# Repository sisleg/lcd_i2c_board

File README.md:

A small interface bord used to connect a LCD character or a OLed character
display that uses the classic HD44780 protocol. Via a I2C buss to any microcontroller.

A MCP23017 from Microchip is used. That ccontroller has two 8 bit ports. One is 
used as the databus to the Display. The other port is used for controll lines (3 bits), contoling a backlight or a external led (1 bit). The last four bits is
used for a simple keybord interface.

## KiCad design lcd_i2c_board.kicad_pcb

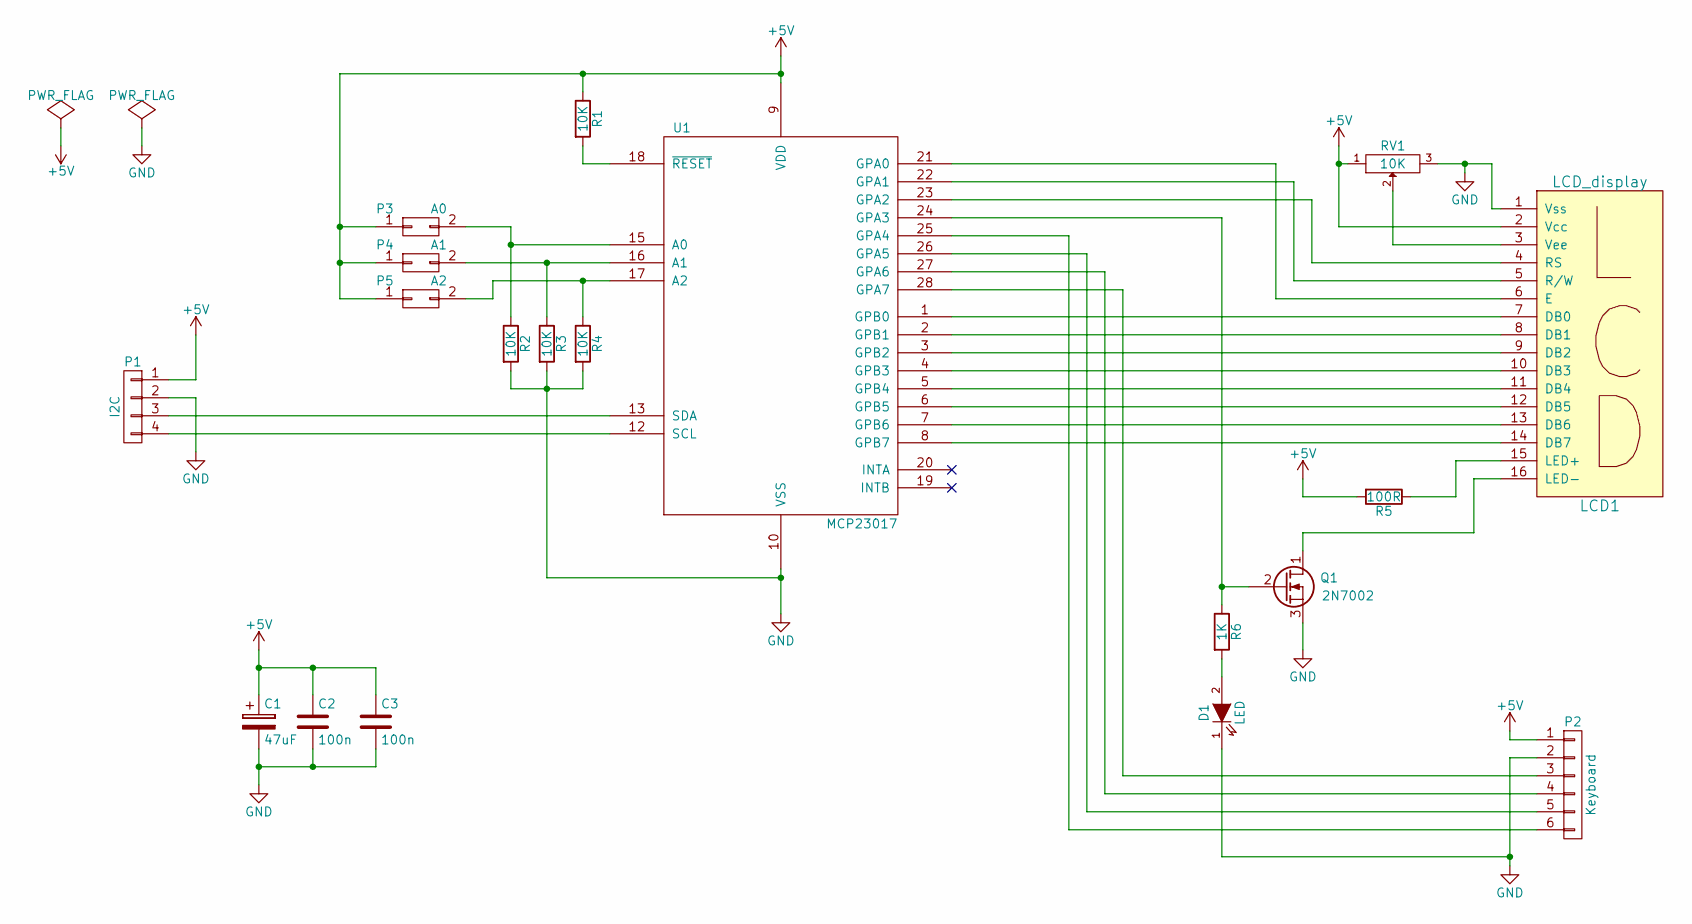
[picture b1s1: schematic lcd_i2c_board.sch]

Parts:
C1: 47uF; c_elec_6.3x7.7
C2, C3: 100n; C_1206_HandSoldering
D1: LED; MOLEX-22-05-3021
LCD1: LCD_display; Pin_Header_Straight_1x16
P1: I2C; MOLEX-22-05-3041
P2: Keyboard; MOLEX-22-05-3061
P3: A0; R_0805_HandSoldering
P4: A1; R_0805_HandSoldering
P5: A2; R_0805_HandSoldering
Q1: 2N7002; SOT-23_Handsoldering
R1, R2, R3, R4: 10K; R_0805_HandSoldering
R5: 100R; R_0805_HandSoldering
R6: 1K; R_0805_HandSoldering
RV1: 10K; Potentiometer_Trimmer-Suntan-TSR-3386P
U1: MCP23017; SOIC-28W_7.5x17.9mm_Pitch1.27mm

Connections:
+5V: C1.1, C2.1, C3.1, LCD1.2 (Vcc), P1.1, P2.1, P3.1, P4.1, P5.1, R1.1, R5.2, RV1.1, U1.9 (VDD)
GND: C1.2, C2.2, C3.2, D1.1 (K), LCD1.1 (Vss), P1.2, P2.2, Q1.3 (S), R2.2, R3.2, R4.2, RV1.3, U1.10 (VSS)
unnamed: D1.2 (A), R6.2
unnamed: LCD1.3 (Vee), RV1.2
unnamed: LCD1.4 (RS), U1.23 (GPA2)
unnamed: LCD1.5 (R/W), U1.22 (GPA1)
unnamed: LCD1.6 (E), U1.21 (GPA0)
unnamed: LCD1.7 (DB0), U1.1 (GPB0)
unnamed: LCD1.8 (DB1), U1.2 (GPB1)
unnamed: LCD1.9 (DB2), U1.3 (GPB2)
unnamed: LCD1.10 (DB3), U1.4 (GPB3)
unnamed: LCD1.11 (DB4), U1.5 (GPB4)
unnamed: LCD1.12 (DB5), U1.6 (GPB5)
unnamed: LCD1.13 (DB6), U1.7 (GPB6)
unnamed: LCD1.14 (DB7), U1.8 (GPB7)
unnamed: LCD1.15 (LED+), R5.1
unnamed: LCD1.16 (LED-), Q1.1 (D)
unnamed: P1.3, U1.13 (SDA)
unnamed: P1.4, U1.12 (SCL)
unnamed: P2.3, U1.28 (GPA7)
unnamed: P2.4, U1.27 (GPA6)
unnamed: P2.5, U1.26 (GPA5)
unnamed: P2.6, U1.25 (GPA4)
unnamed: P3.2, R2.1, U1.15 (A0)
unnamed: P4.2, R3.1, U1.16 (A1)
unnamed: P5.2, R4.1, U1.17 (A2)
unnamed: Q1.2 (G), R6.1, U1.24 (GPA3)
unnamed: R1.2, U1.18 (~RESET)

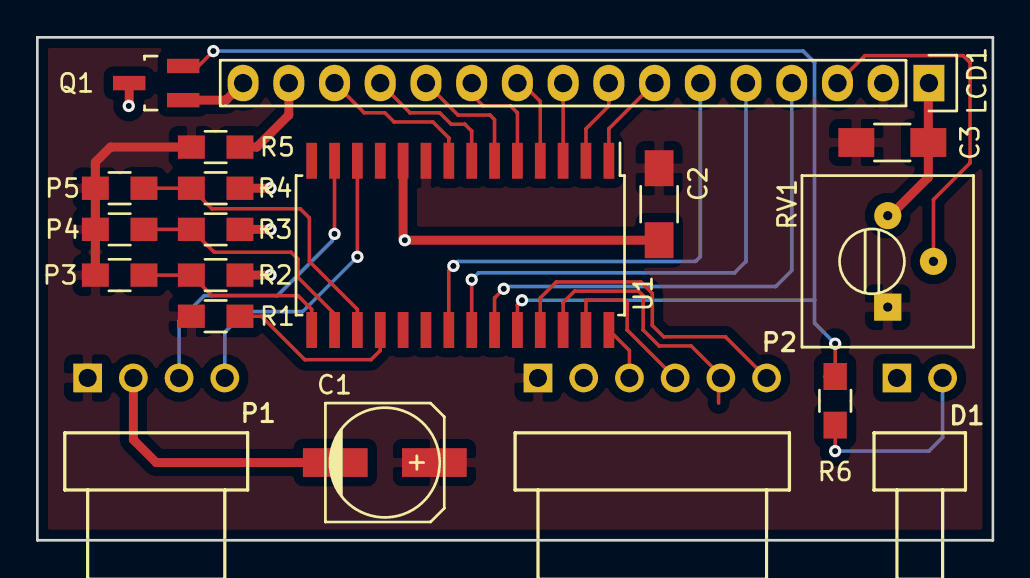
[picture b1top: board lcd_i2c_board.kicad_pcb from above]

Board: 2 copper layers, 53.1 x 27.9 mm, 19 parts (0 on the bottom side), 28 nets.

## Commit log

2016-10-19 First commit, an order to OSH Park is done using this release.
2016-10-19 Change reference placement because component values did not show up on OSH park board.
